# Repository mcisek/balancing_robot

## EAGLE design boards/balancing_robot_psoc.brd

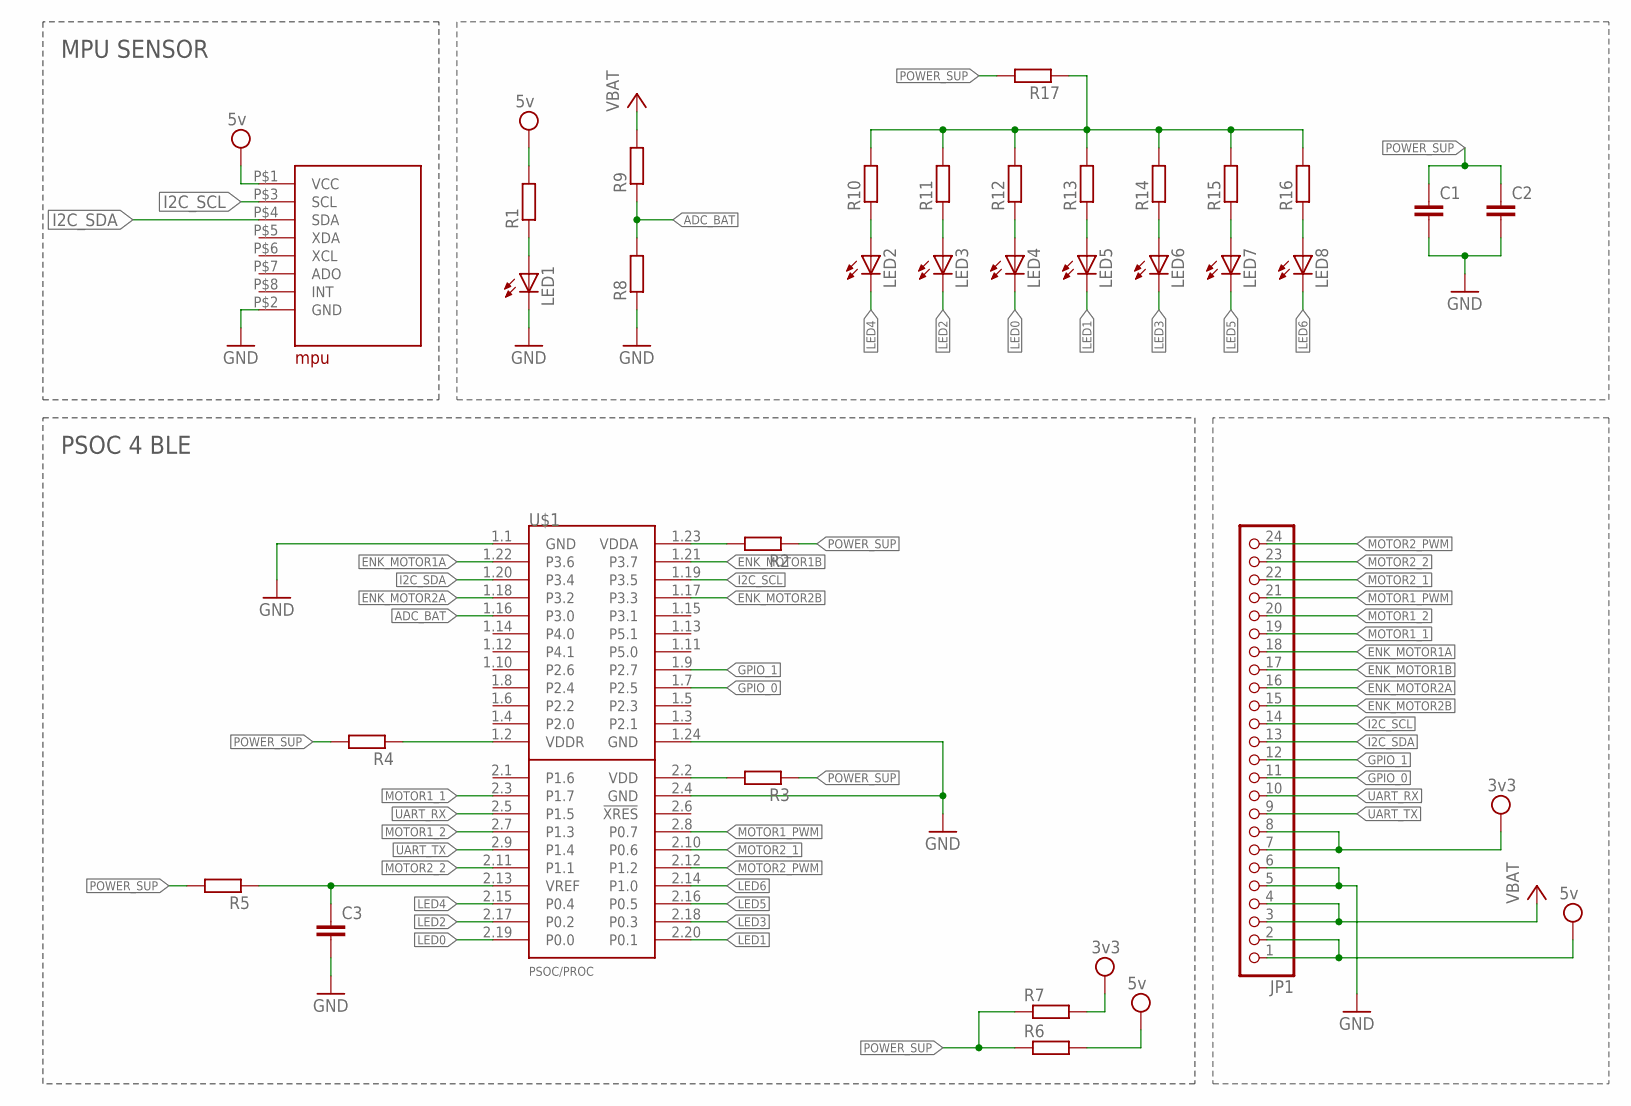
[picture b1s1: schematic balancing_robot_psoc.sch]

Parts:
C1, C3: C-EUC0603; C0603
C2: C-EUC0805; C0805
JP1: PINHD-1X24; 1X24
LED1, LED2, LED3, LED4, LED5, LED6, LED7, LED8: LEDCHIP-LED0603; CHIP-LED0603
R1, R2, R3, R4, R5, R6, R7, R8, R9, R10, R11, R12, R13, R14, R15, R16, R17: R-EU_R0603; R0603
U$1: PSOC/PROC; PSOC/PROC_SOCKET
U$5: MPU

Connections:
3V3: JP1.7, JP1.8, R7.2
5V: JP1.1, JP1.2, R1.2, R6.2, U$5.P$1 (VCC)
ADC_BAT: R8.2, R9.1, U$1.1.16 (P3.0)
CONN1: R10.2, R11.2, R12.2, R13.2, R14.2, R15.2, R16.2, R17.1
ENK_MOTOR1A: JP1.18, U$1.1.22 (P3.6)
ENK_MOTOR1B: JP1.17, U$1.1.21 (P3.7)
ENK_MOTOR2A: JP1.16, U$1.1.18 (P3.2)
ENK_MOTOR2B: JP1.15, U$1.1.17 (P3.3)
GND: C1.2, C2.2, C3.2, JP1.5, JP1.6, LED1.C, R8.1, U$1.1.1 (GND), U$1.1.24 (GND), U$1.2.4 (GND), U$5.P$2 (GND)
GPIO_0: JP1.11, U$1.1.7 (P2.5)
GPIO_1: JP1.12, U$1.1.9 (P2.7)
I2C_SCL: JP1.14, U$1.1.19 (P3.5), U$5.P$3 (SCL)
I2C_SDA: JP1.13, U$1.1.20 (P3.4), U$5.P$4 (SDA)
LED0: LED4.C, U$1.2.19 (P0.0)
LED1: LED5.C, U$1.2.20 (P0.1)
LED2: LED3.C, U$1.2.17 (P0.2)
LED3: LED6.C, U$1.2.18 (P0.3)
LED4: LED2.C, U$1.2.15 (P0.4)
LED5: LED7.C, U$1.2.16 (P0.5)
LED6: LED8.C, U$1.2.14 (P1.0)
MOTOR1_1: JP1.19, U$1.2.3 (P1.7)
MOTOR1_2: JP1.20, U$1.2.7 (P1.3)
MOTOR1_PWM: JP1.21, U$1.2.8 (P0.7)
MOTOR2_1: JP1.22, U$1.2.10 (P0.6)
MOTOR2_2: JP1.23, U$1.2.11 (P1.1)
MOTOR2_PWM: JP1.24, U$1.2.12 (P1.2)
unnamed: R2.2, U$1.1.23 (VDDA)
unnamed: C3.1, R5.1, U$1.2.13 (VREF)
unnamed: R3.2, U$1.2.2 (VDD)
unnamed: R4.1, U$1.1.2 (VDDR)
unnamed: LED2.A, R10.1
unnamed: LED3.A, R11.1
unnamed: LED4.A, R12.1
unnamed: LED5.A, R13.1
unnamed: LED6.A, R14.1
unnamed: LED7.A, R15.1
unnamed: LED8.A, R16.1
unnamed: LED1.A, R1.1
POWER_SUP: C1.1, C2.1, R2.1, R3.1, R4.2, R5.2, R6.1, R7.1, R17.2
UART_RX: JP1.10, U$1.2.5 (P1.5)
UART_TX: JP1.9, U$1.2.9 (P1.4)
VCC: JP1.3, JP1.4, R9.2

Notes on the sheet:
PSOC 4 BLE
MPU SENSOR

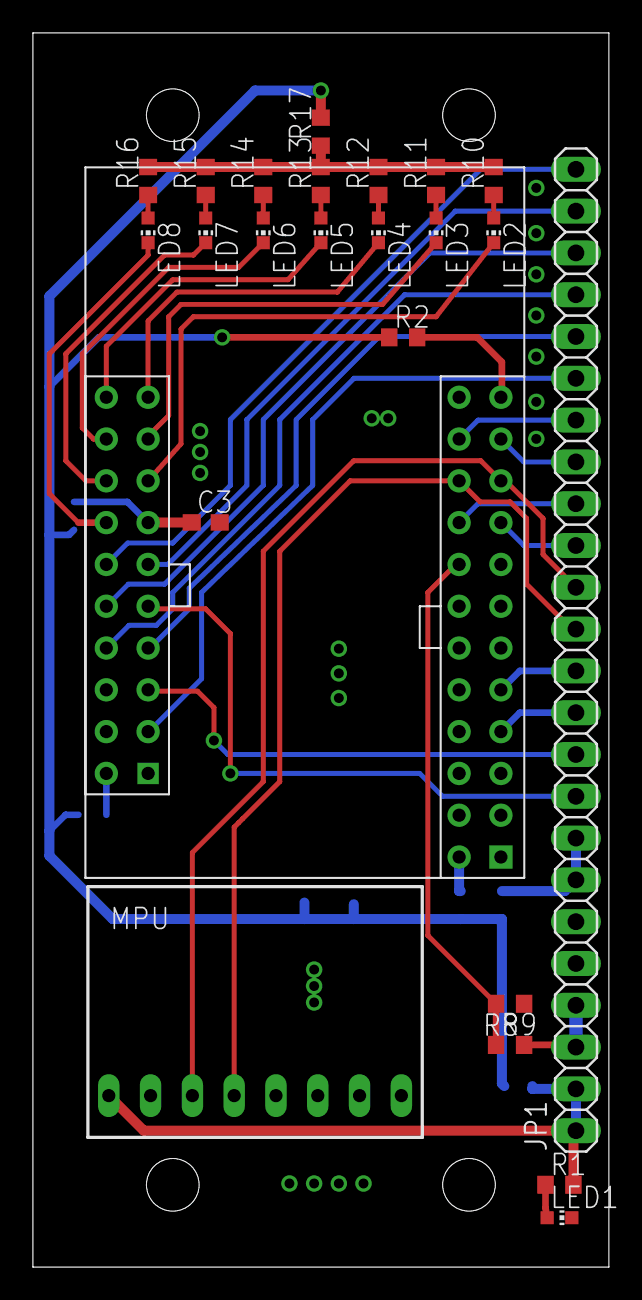
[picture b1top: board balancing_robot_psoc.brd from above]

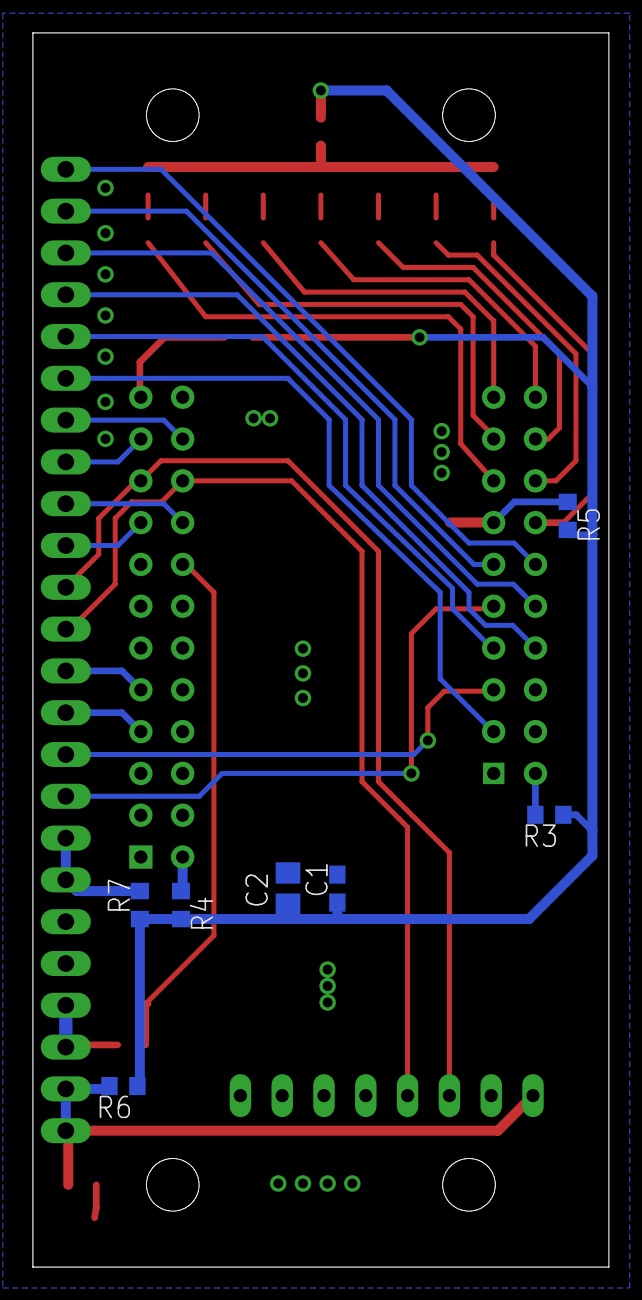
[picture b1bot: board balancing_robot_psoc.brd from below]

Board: 2 copper layers, 35.0 x 75.0 mm, 31 parts (7 on the bottom side), 42 nets.

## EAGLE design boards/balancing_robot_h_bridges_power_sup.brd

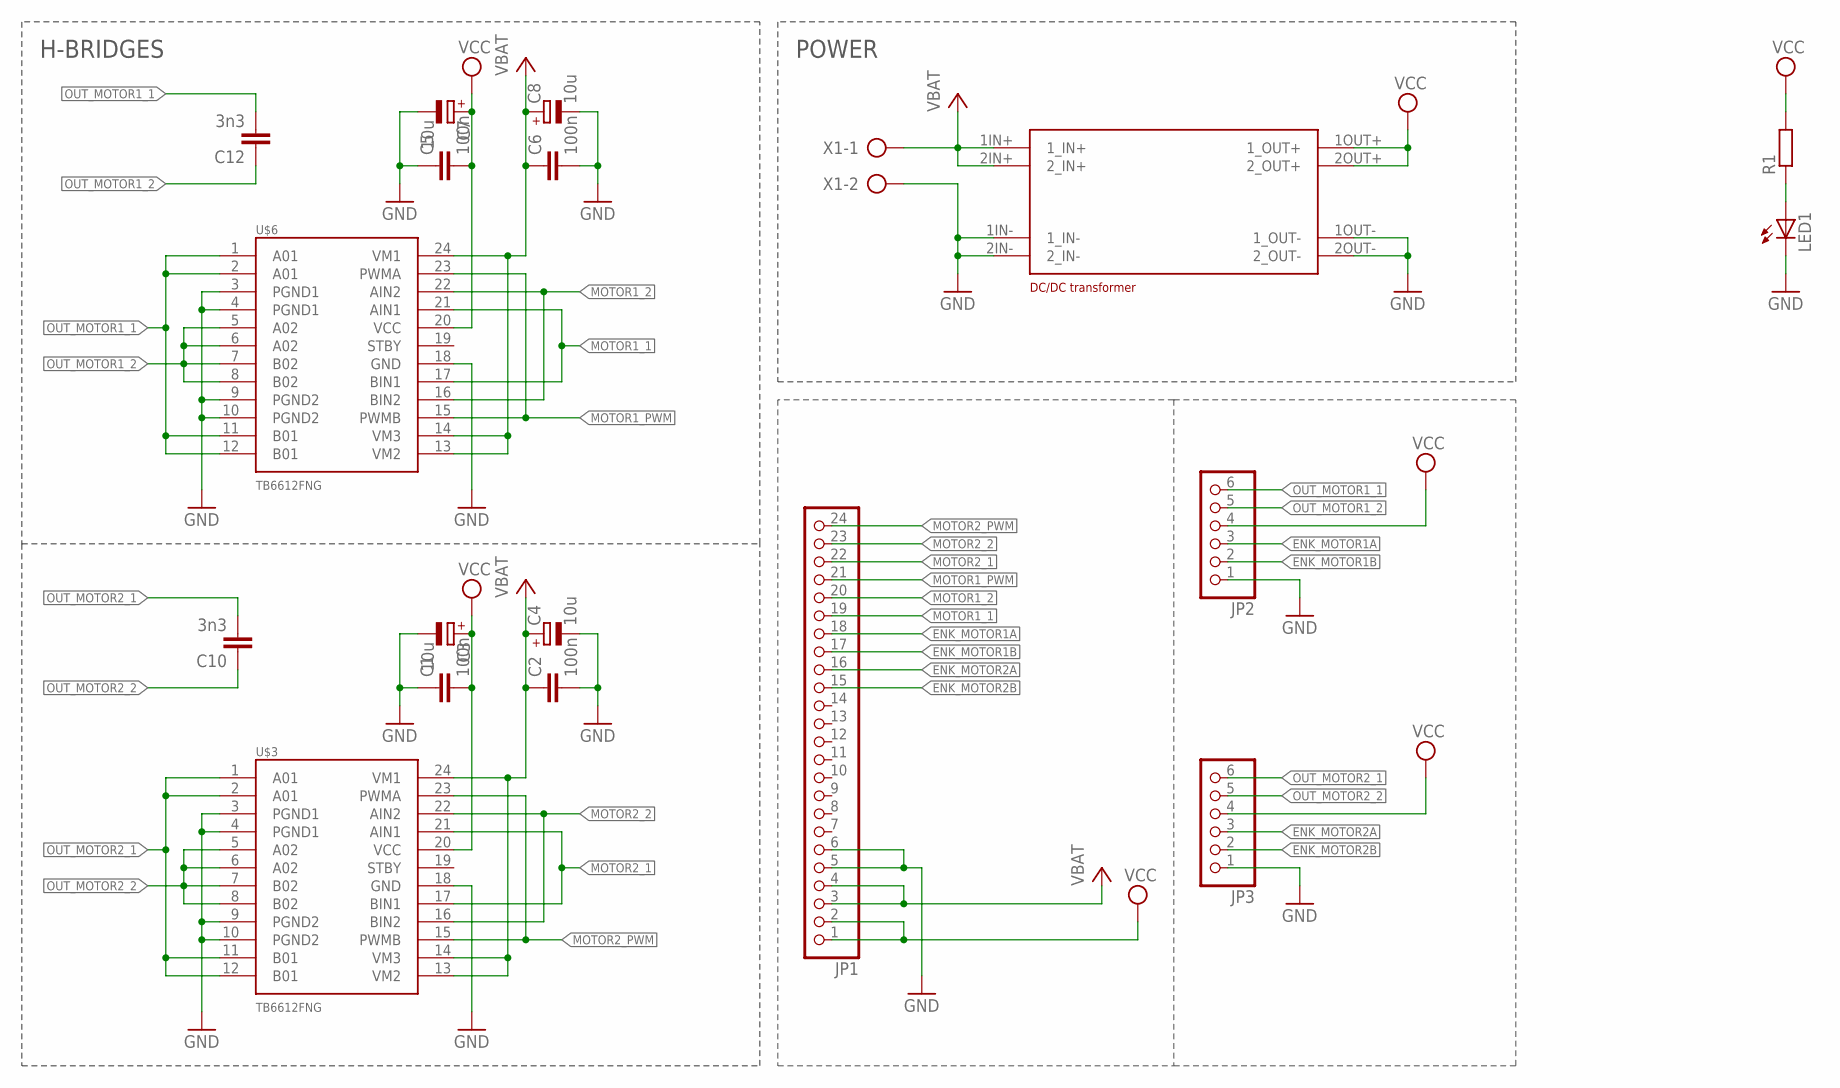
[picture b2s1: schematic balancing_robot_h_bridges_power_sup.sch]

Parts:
C1, C2, C5, C6: 100n; C0603
C3, C4, C7, C8: 10u; 153CLV-0405
C10, C12: 3n3; C0603
JP1: PINHD-1X24; 1X24
JP2, JP3: PINHD-1X6; 1X06
LED1: LEDCHIP-LED0603; CHIP-LED0603
R1: R-EU_R0603; R0603
U$3, U$6: TB6612FNG; SSOP24
U$4: TRANSFORMER
X1: AK500/2

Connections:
ENK_MOTOR1A: JP1.18, JP2.3
ENK_MOTOR1B: JP1.17, JP2.2
ENK_MOTOR2A: JP1.16, JP3.3
ENK_MOTOR2B: JP1.15, JP3.2
GND: C1.1, C2.2, C3.-, C4.-, C5.1, C6.2, C7.-, C8.-, JP1.5, JP1.6, JP2.1, JP3.1, LED1.C, U$3.3 (PGND1), U$3.4 (PGND1), U$3.9 (PGND2), U$3.10 (PGND2), U$3.18 (GND), U$4.1IN- (1_IN-), U$4.1OUT- (1_OUT-), U$4.2IN- (2_IN-), U$4.2OUT- (2_OUT-), U$6.3 (PGND1), U$6.4 (PGND1), U$6.9 (PGND2), U$6.10 (PGND2), U$6.18 (GND), X1.2
MOTOR1_1: JP1.19, U$6.17 (BIN1), U$6.21 (AIN1)
MOTOR1_2: JP1.20, U$6.16 (BIN2), U$6.22 (AIN2)
MOTOR1_PWM: JP1.21, U$6.15 (PWMB), U$6.23 (PWMA)
MOTOR2_1: JP1.22, U$3.17 (BIN1), U$3.21 (AIN1)
MOTOR2_2: JP1.23, U$3.16 (BIN2), U$3.22 (AIN2)
MOTOR2_PWM: JP1.24, U$3.15 (PWMB), U$3.23 (PWMA)
unnamed: LED1.A, R1.1
OUT_MOTOR1_1: C12.2, JP2.6, U$6.1 (A01), U$6.2 (A01), U$6.11 (B01), U$6.12 (B01)
OUT_MOTOR1_2: C12.1, JP2.5, U$6.5 (A02), U$6.6 (A02), U$6.7 (B02), U$6.8 (B02)
OUT_MOTOR2_1: C10.2, JP3.6, U$3.1 (A01), U$3.2 (A01), U$3.11 (B01), U$3.12 (B01)
OUT_MOTOR2_2: C10.1, JP3.5, U$3.5 (A02), U$3.6 (A02), U$3.7 (B02), U$3.8 (B02)
VCC: C1.2, C2.1, C3.+, C4.+, C5.2, C6.1, C7.+, C8.+, JP1.1, JP1.2, JP1.3, JP1.4, JP2.4, JP3.4, R1.2, U$3.13 (VM2), U$3.14 (VM3), U$3.20 (VCC), U$3.24 (VM1), U$4.1IN+ (1_IN+), U$4.1OUT+ (1_OUT+), U$4.2IN+ (2_IN+), U$4.2OUT+ (2_OUT+), U$6.13 (VM2), U$6.14 (VM3), U$6.20 (VCC), U$6.24 (VM1), X1.1

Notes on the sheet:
POWER
H-BRIDGES

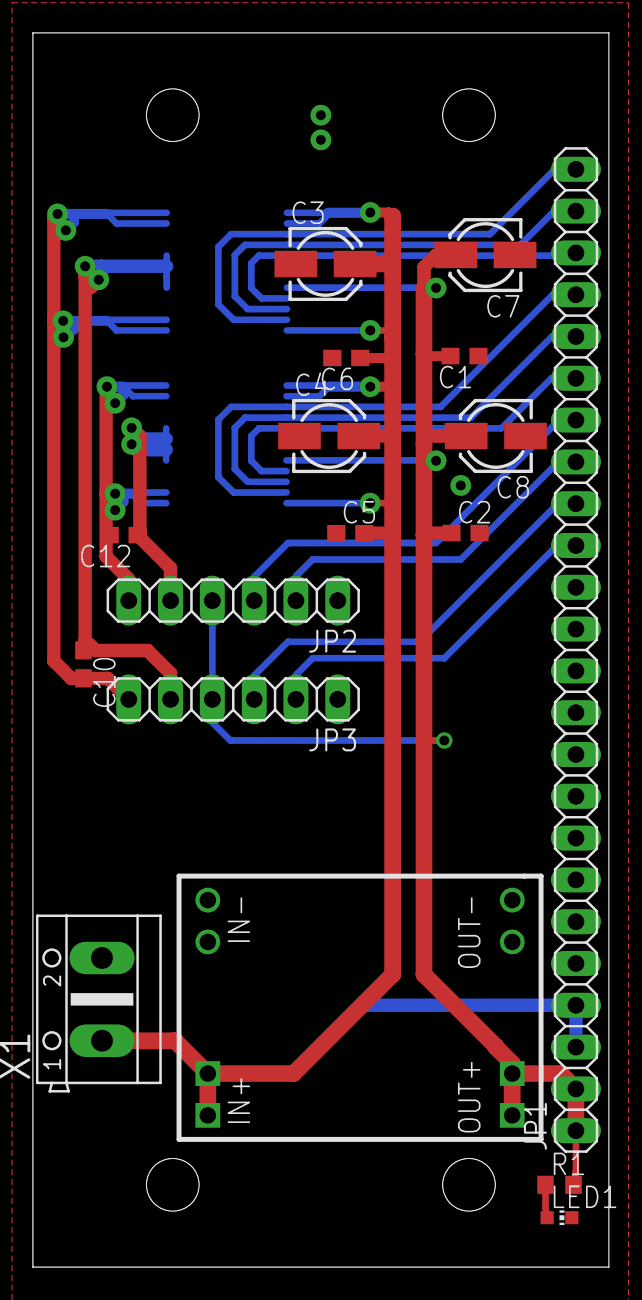
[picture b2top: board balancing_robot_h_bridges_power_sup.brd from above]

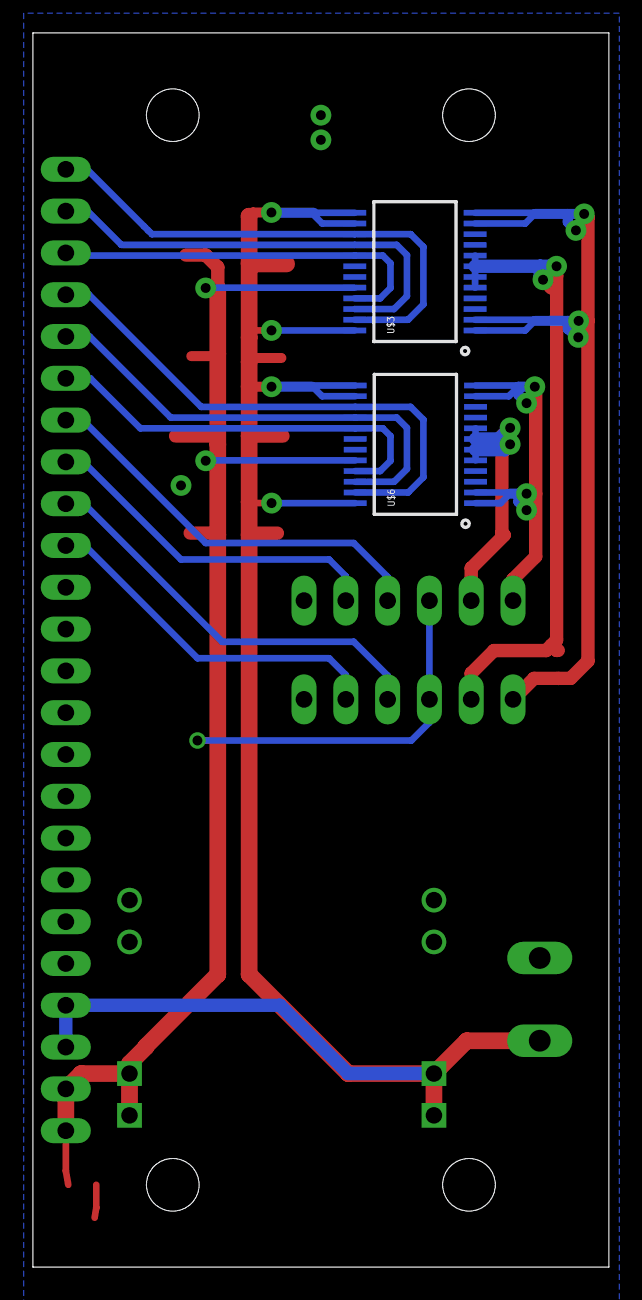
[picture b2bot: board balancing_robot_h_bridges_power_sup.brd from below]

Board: 2 copper layers, 35.0 x 75.0 mm, 19 parts (2 on the bottom side), 17 nets.

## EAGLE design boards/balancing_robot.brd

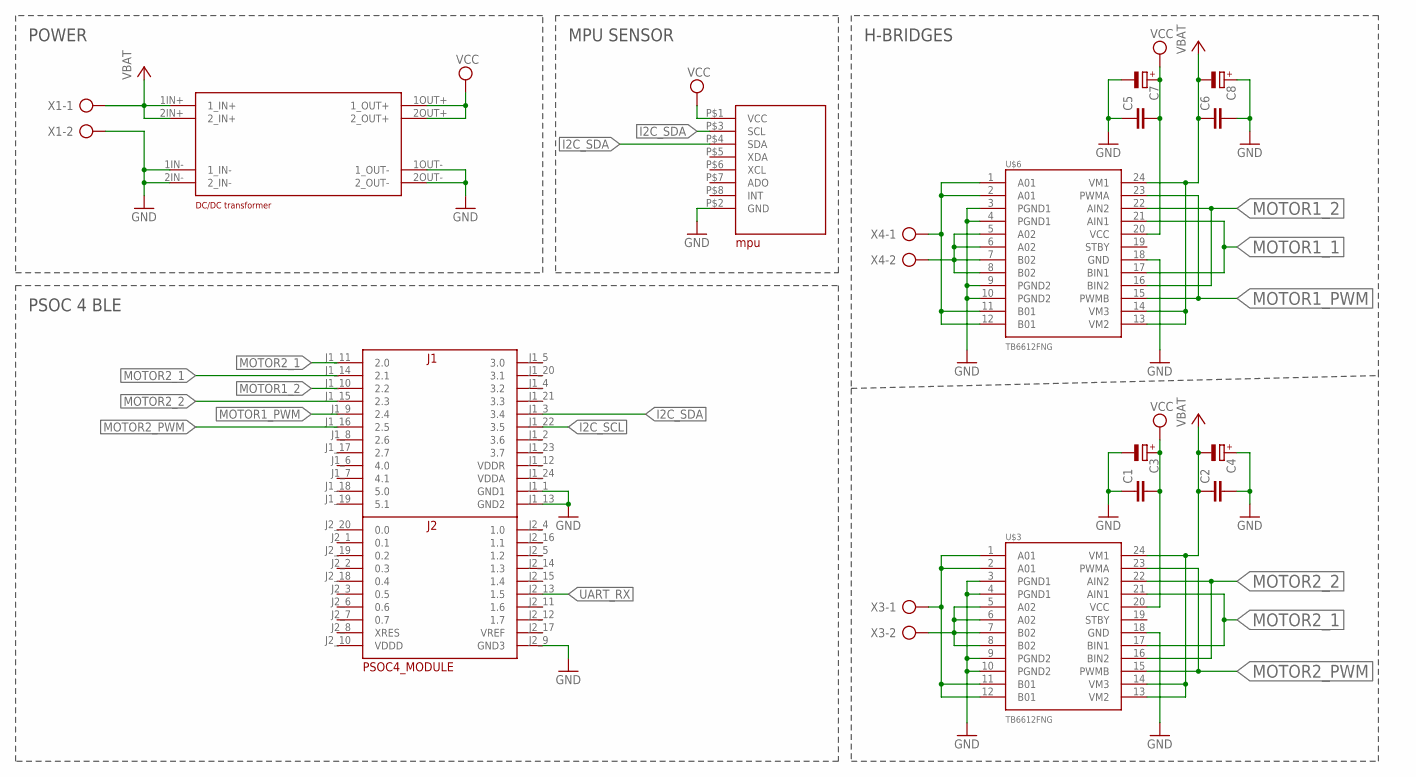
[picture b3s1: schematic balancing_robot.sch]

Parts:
C1, C2, C5, C6: C-EUC0603; C0603
C3, C4, C7, C8: CPOL-EU153CLV-0405; 153CLV-0405
U$1: PSOC4_MODULE
U$3, U$6: TB6612FNG; SSOP24
U$4: TRANSFORMER
U$5: MPU
X1, X3, X4: AK500/2

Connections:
GND: C1.1, C2.2, C3.-, C4.+, C5.1, C6.2, C7.-, C8.+, U$1.J1_1 (GND1), U$1.J1_13 (GND2), U$1.J2_9 (GND3), U$3.18 (GND), U$4.1IN- (1_IN-), U$4.1OUT- (1_OUT-), U$4.2IN- (2_IN-), U$4.2OUT- (2_OUT-), U$5.P$2 (GND), U$6.18 (GND), X1.2
I2C_SCL: U$1.J1_22 (3.5)
I2C_SDA: U$1.J1_3 (3.4), U$5.P$3 (SCL), U$5.P$4 (SDA)
MOTOR1_1: U$1.J1_11 (2.0), U$6.17 (BIN1), U$6.21 (AIN1)
MOTOR1_2: U$1.J1_10 (2.2), U$6.16 (BIN2), U$6.22 (AIN2)
MOTOR1_PWM: U$1.J1_9 (2.4), U$6.15 (PWMB), U$6.23 (PWMA)
MOTOR2_1: U$1.J1_14 (2.1), U$3.17 (BIN1), U$3.21 (AIN1)
MOTOR2_2: U$1.J1_15 (2.3), U$3.16 (BIN2), U$3.22 (AIN2)
MOTOR2_PWM: U$1.J1_16 (2.5), U$3.15 (PWMB), U$3.23 (PWMA)
unnamed: U$3.1 (A01), U$3.2 (A01), U$3.11 (B01), U$3.12 (B01), X3.1
unnamed: U$3.5 (A02), U$3.6 (A02), U$3.7 (B02), U$3.8 (B02), X3.2
unnamed: U$3.3 (PGND1), U$3.4 (PGND1), U$3.9 (PGND2), U$3.10 (PGND2), U$6.3 (PGND1), U$6.4 (PGND1), U$6.9 (PGND2), U$6.10 (PGND2)
unnamed: U$6.1 (A01), U$6.2 (A01), U$6.11 (B01), U$6.12 (B01), X4.1
unnamed: U$6.5 (A02), U$6.6 (A02), U$6.7 (B02), U$6.8 (B02), X4.2
UART_RX: U$1.J2_13 (1.5)
VCC: C1.2, C2.1, C3.+, C4.-, C5.2, C6.1, C7.+, C8.-, U$3.13 (VM2), U$3.14 (VM3), U$3.20 (VCC), U$3.24 (VM1), U$4.1IN+ (1_IN+), U$4.1OUT+ (1_OUT+), U$4.2IN+ (2_IN+), U$4.2OUT+ (2_OUT+), U$5.P$1 (VCC), U$6.13 (VM2), U$6.14 (VM3), U$6.20 (VCC), U$6.24 (VM1), X1.1

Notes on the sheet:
POWER
PSOC 4 BLE
MPU SENSOR
H-BRIDGES

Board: 2 copper layers, 16 parts (0 on the bottom side), 14 nets, no tracks yet.

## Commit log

2015-11-04 Init, working communication with MPU sensor
2015-11-30 h-bridges and psu board
2015-11-30 finished h-bridges and psu board, rev. 1
2015-11-30 updated bridge board
2015-12-07 PsoC and MPU board finished
2015-12-07 added capacitors on power sup line on psoc board
2015-12-07 final changes of boards - production version
2015-12-10 satland production version of boards
2015-12-31 Added motor function, soft in files, leds, i2c communication problem

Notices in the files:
parts and their libraries:
SparkFun-PowerIC: Licensing: Creative Commons ShareAlike 4.0 International - https://creativecommons.org/licenses/by-sa/4.0
